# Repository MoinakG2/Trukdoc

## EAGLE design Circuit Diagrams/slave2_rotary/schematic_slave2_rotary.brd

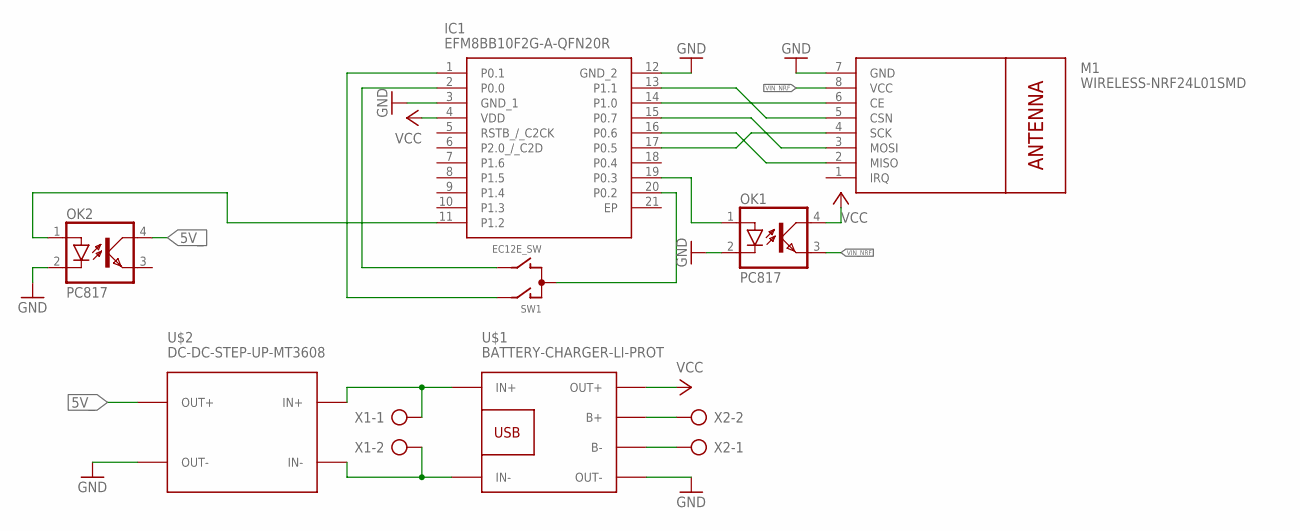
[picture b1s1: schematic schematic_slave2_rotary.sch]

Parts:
IC1: EFM8BB10F2G-A-QFN20R; EFM8BB10F2GAQFN20R
M1: WIRELESS-NRF24L01SMD; WIRELESS-NRF24L01-SMD
OK1, OK2: PC817; DIL04
SW1: EC12E_SW; ALPS_EC12E_SW
U$1: BATTERY-CHARGER-LI-PROT
U$2: DC-DC-STEP-UP-MT3608
X1, X2: AK500/2-H

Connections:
5V_: OK2.4 (COL), U$2.OUT+
GND: IC1.3 (GND_1), IC1.12 (GND_2), M1.7 (GND), OK1.2 (C), OK2.2 (C), U$1.OUT-, U$2.OUT-
IN+: U$1.IN+, U$2.IN+, X1.1
IN-: U$1.IN-, U$2.IN-, X1.2
unnamed: IC1.11 (P1.2), OK2.1 (A)
unnamed: IC1.2 (P0.0), SW1.B
unnamed: IC1.17 (P0.5), M1.4 (SCK)
unnamed: IC1.16 (P0.6), M1.2 (MISO)
unnamed: IC1.15 (P0.7), M1.3 (MOSI)
unnamed: IC1.14 (P1.0), M1.6 (CE)
unnamed: IC1.13 (P1.1), M1.5 (CSN)
unnamed: IC1.19 (P0.3), OK1.1 (A)
unnamed: U$1.B+, X2.2
unnamed: IC1.1 (P0.1), SW1.A
unnamed: IC1.20 (P0.2), SW1.C
unnamed: U$1.B-, X2.1
VCC: IC1.4 (VDD), OK1.4 (COL), U$1.OUT+
VIN_NRF: M1.8 (VCC), OK1.3 (EMIT)

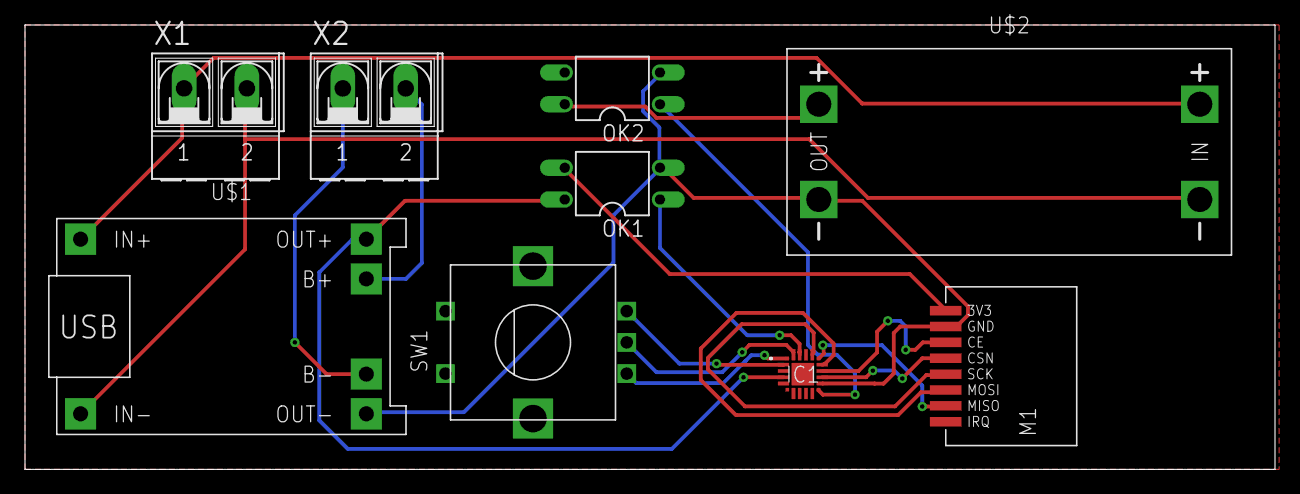
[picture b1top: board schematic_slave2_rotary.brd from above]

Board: 2 copper layers, 100.0 x 35.5 mm, 9 parts (0 on the bottom side), 18 nets.

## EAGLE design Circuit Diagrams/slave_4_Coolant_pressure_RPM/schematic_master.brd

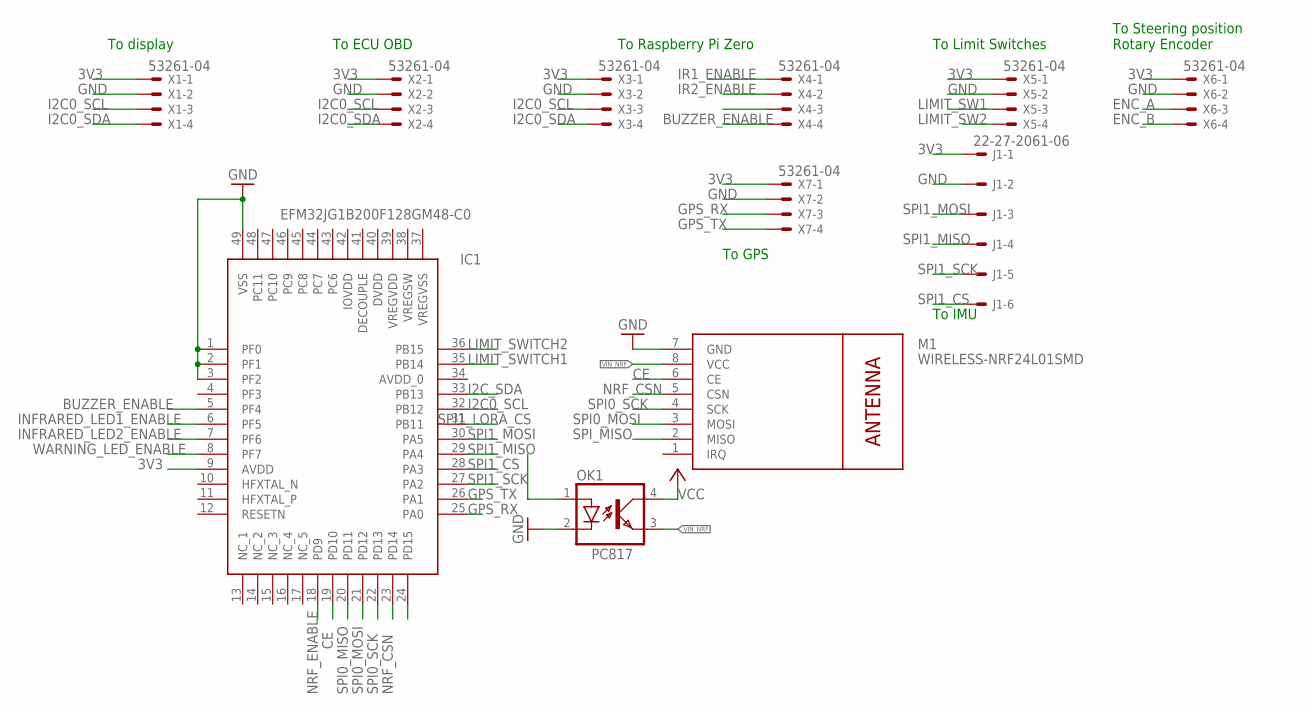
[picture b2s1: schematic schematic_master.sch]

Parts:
IC1: EFM32JG1B200F128GM48-C0; QFN50P700X700X90-49N
J1: 22-27-2061-06; 6410-06
M1: WIRELESS-NRF24L01SMD; WIRELESS-NRF24L01-SMD
OK1: PC817; DIL04
X1, X2, X3, X4, X5, X6, X7: 53261-04

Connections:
3V3: IC1.9 (AVDD), J1.1, X1.1, X2.1, X3.1, X5.1, X6.1, X7.1
BUZZER_ENABLE: IC1.5 (PF4), X4.3
CE: IC1.19 (PD10), M1.6 (CE)
ENC_A: X6.3
ENC_B: X6.4
GND: IC1.1 (PF0), IC1.2 (PF1), IC1.3 (PF2), IC1.49 (VSS), J1.2, M1.7 (GND), OK1.2 (C), X1.2, X2.2, X3.2, X5.2, X6.2, X7.2
GPS_RX: IC1.25 (PA0), X7.3
GPS_TX: IC1.26 (PA1), X7.4
I2C0_SCL: IC1.32 (PB12), X1.3, X2.3, X3.3
I2C0_SDA: X1.4, X2.4, X3.4
I2C_SDA: IC1.33 (PB13)
INFRARED_LED1_ENABLE: IC1.6 (PF5)
INFRARED_LED2_ENABLE: IC1.7 (PF6)
IR1_ENABLE: X4.1
IR2_ENABLE: X4.2
LIMIT_SW1: X5.3
LIMIT_SW2: X5.4
LIMIT_SWITCH1: IC1.35 (PB14)
LIMIT_SWITCH2: IC1.36 (PB15)
NRF_CSN: IC1.23 (PD14), M1.5 (CSN)
NRF_ENABLE: IC1.18 (PD9)
SPI0_MISO: IC1.20 (PD11)
SPI0_MOSI: IC1.21 (PD12), M1.3 (MOSI)
SPI0_SCK: IC1.22 (PD13), M1.4 (SCK)
SPI1_CS: IC1.28 (PA3), J1.6
SPI1_LORA_CS: IC1.31 (PB11)
SPI1_MISO: IC1.29 (PA4), J1.4
SPI1_MOSI: IC1.30 (PA5), J1.3
SPI1_SCK: IC1.27 (PA2), J1.5
SPI_MISO: M1.2 (MISO)
VCC: OK1.4 (COL)
VIN_NRF: M1.8 (VCC), OK1.3 (EMIT)
WARNING_LED_ENABLE: IC1.8 (PF7)

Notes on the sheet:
To GPS
To IMU
To display
To Raspberry Pi Zero
To ECU OBD
To Limit Switches
To Steering position Rotary Encoder

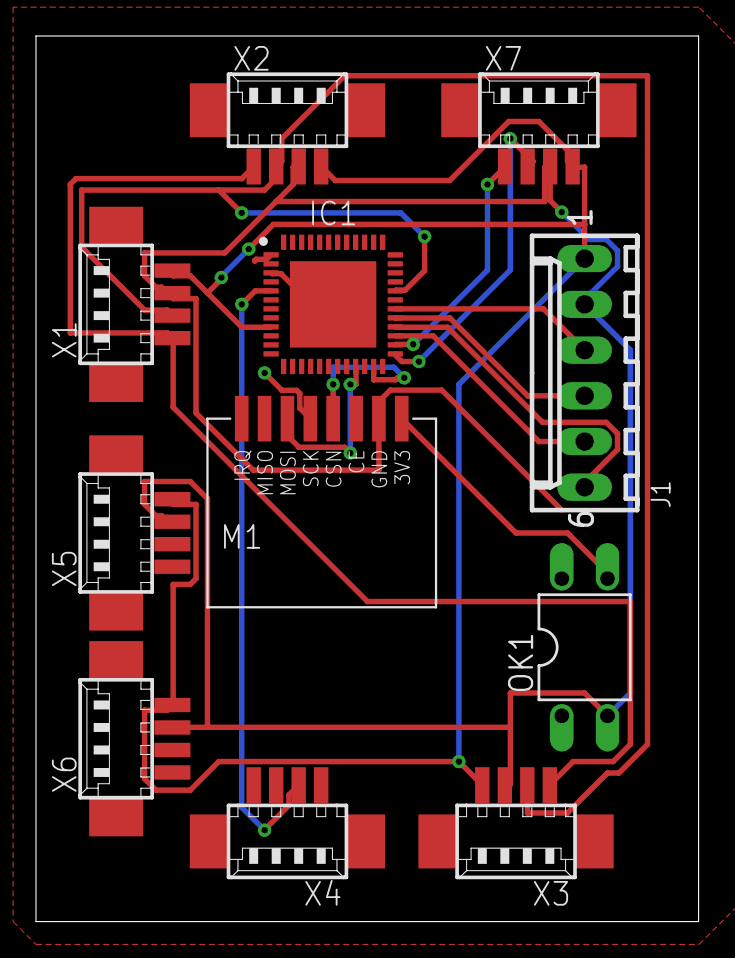
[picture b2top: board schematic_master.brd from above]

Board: 2 copper layers, 36.8 x 49.2 mm, 11 parts (0 on the bottom side), 16 nets.

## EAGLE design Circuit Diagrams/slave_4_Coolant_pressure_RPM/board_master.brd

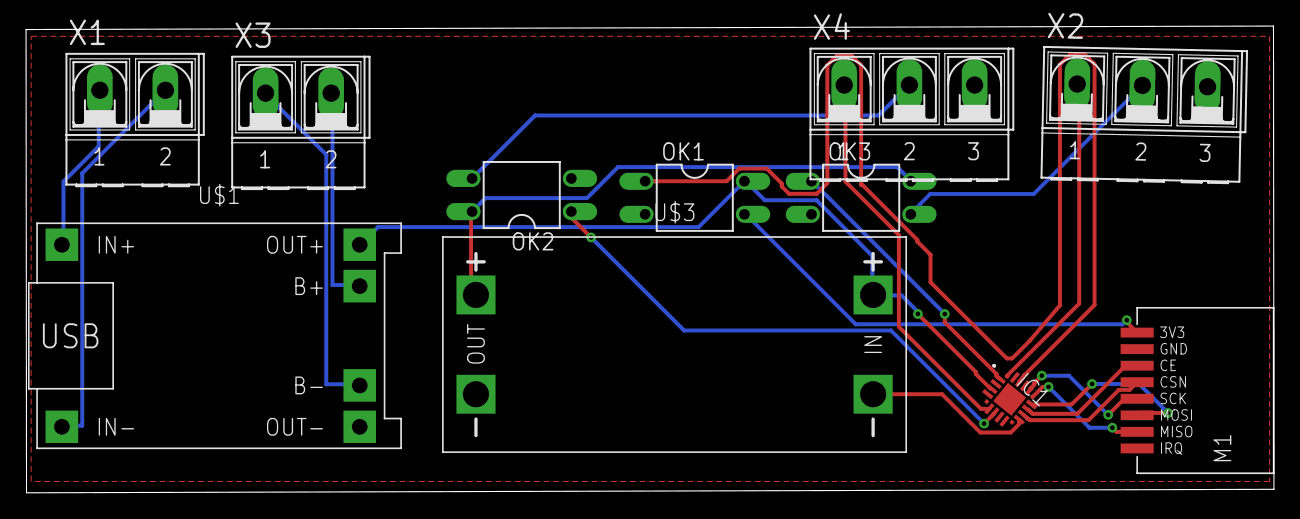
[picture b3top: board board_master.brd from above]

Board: 2 copper layers, 95.8 x 35.8 mm, 11 parts (0 on the bottom side), 20 nets.

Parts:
IC1: EFM8BB10F2G-A-QFN20R; EFM8BB10F2GAQFN20R
M1: WIRELESS-NRF24L01SMD; WIRELESS-NRF24L01-SMD
OK1, OK2, OK3: PC817; DIL04
U$1: BATTERY-CHARGER-LI-PROT
U$3: DC-DC-STEP-UP-MT3608
X1, X3: AK500/2-H
X2, X4: AK500/3-H

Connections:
GND: IC1.12, M1.7, OK1.2, OK2.2, OK3.2, U$1.OUT-, U$3.IN-, U$3.OUT-, X2.3, X4.3
IN+: U$1.IN+, X1.1
IN-: U$1.IN-, X1.2
unnamed: IC1.2, OK3.1
unnamed: IC1.1, X2.1
unnamed: IC1.17, M1.4
unnamed: IC1.16, M1.2
unnamed: IC1.15, M1.3
unnamed: IC1.14, M1.6
unnamed: IC1.13, M1.5
unnamed: IC1.19, OK1.1
unnamed: OK3.3, X2.2
unnamed: U$1.B-, X3.1
unnamed: U$1.B+, X3.2
unnamed: OK2.4, OK3.4, U$3.OUT+
unnamed: IC1.8, OK2.1
unnamed: IC1.7, X4.1
unnamed: OK2.3, X4.2
VCC: IC1.4, OK1.4, U$1.OUT+, U$3.IN+
VIN_NRF: M1.8, OK1.3

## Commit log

2022-05-11 Uploaded all project files
2022-05-23 Added C++ library for Edge impulse model of drowsiness detection

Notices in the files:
parts and their libraries:
diy-modules_1: Released under the Creative Commons Attribution 4.0 International License: http://creativecommons.org/licenses/by/4.0
